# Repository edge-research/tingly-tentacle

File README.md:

# tingly-tentacle

# pololu stepper motor

- 1208 Stepper Motor: Bipolar, 200 Steps/Rev, 35×28mm, 10V, 0.5 A/Phase = 12.95
- https://www.pololu.com/product/1208

# pololu motor driver

- 2970 AMIS-30543 Stepper Motor Driver Carrier = 19.95
- https://www.pololu.com/product/2970
- http://www.onsemi.com/pub/Collateral/AMIS-30543-D.PDF
- https://github.com/pololu/amis-30543-arduino/

# blue robotics TSYS01

- https://github.com/bluerobotics/BlueRobotics_TSYS01_Library

# blue robotics MS5837

- http://docs.bluerobotics.com/bar30/
- https://github.com/bluerobotics/BlueRobotics_MS5837_Library

peristaltic pump system:
http://www.maschinenreich.com/wp-content/uploads/2017/03/XP88-Manual-A4-170320.pdf

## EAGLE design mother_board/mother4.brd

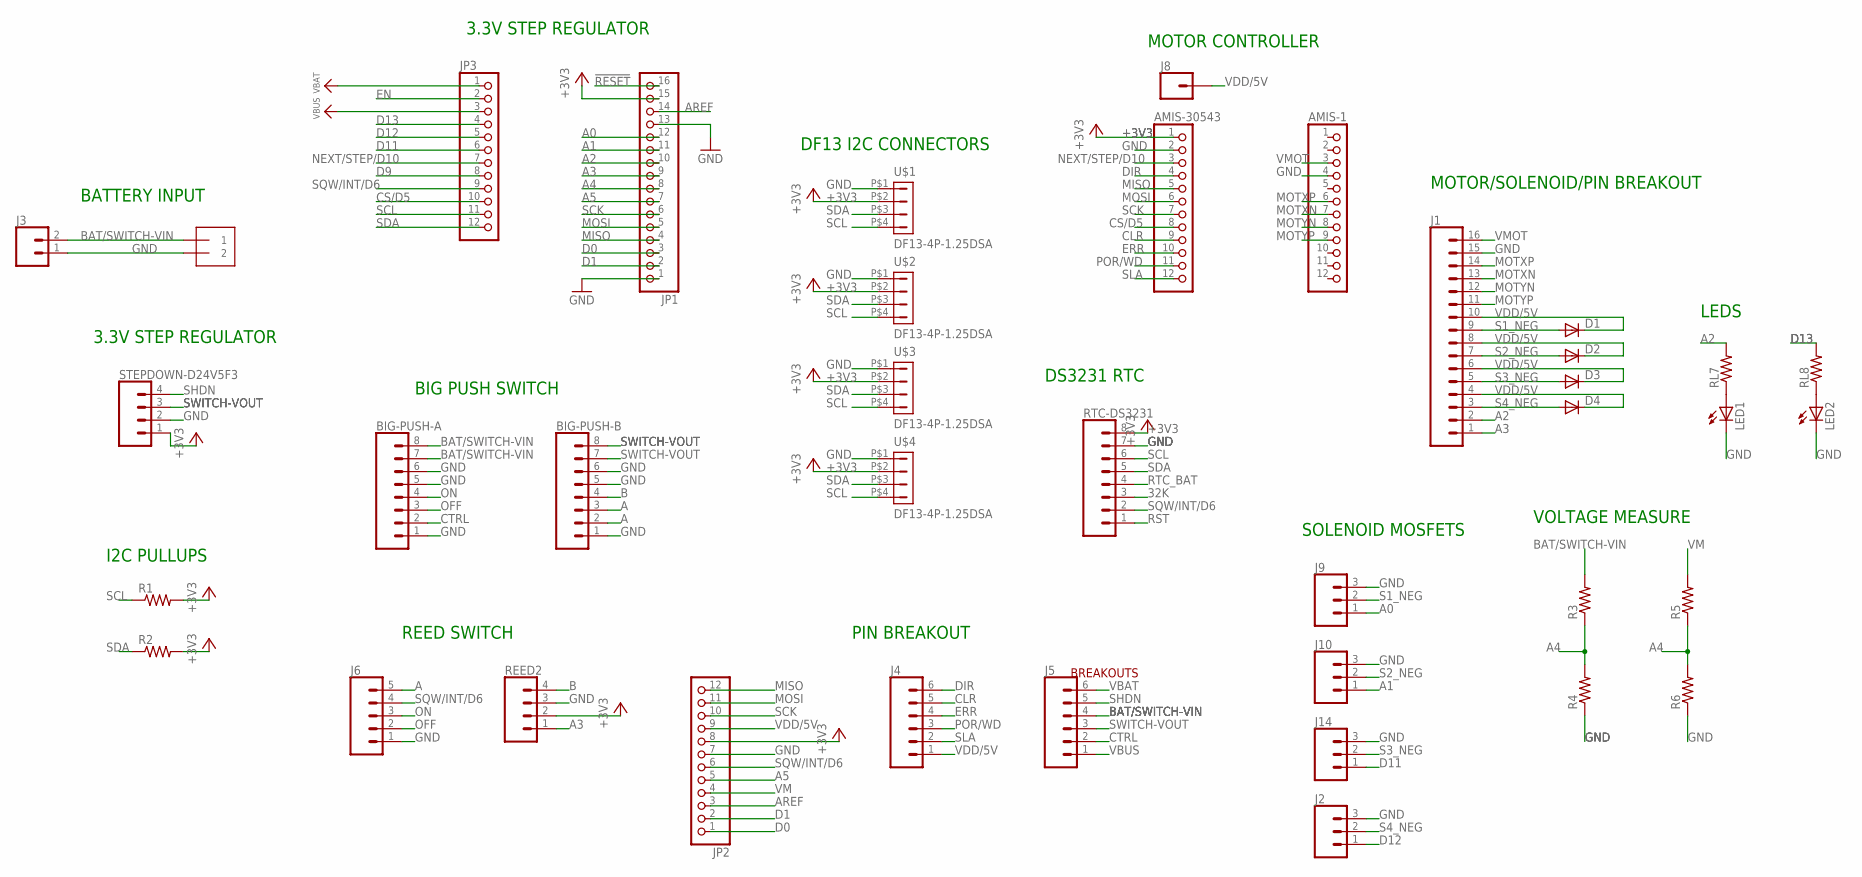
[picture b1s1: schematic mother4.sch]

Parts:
AMIS-1, AMIS-30543: PINHD-1X12-CB; 1X12-CB
BAT: 1X2-3.5MM
BIG-PUSH-A: CONN_08"; 1X08
BIG-PUSH-B: CONN_08"; 1X08
D1, D2, D3, D4: 1N4148DO35-7; DO35-7
J1: CONN_16; 1X16
J2, J9, J10, J14: CONN_03; 1X03
J3: CONN_02; 1X02
J4, J5: CONN_06SILK_FEMALE_PTH; 1X06
J6: CONN_05; 1X05
J8: CONN_01; 1X01
JP1: HEADER-1X16ROUND; 1X16_ROUND
JP2, JP3: HEADER-1X12; 1X12_ROUND
LED1, LED2: LED5MM
R1, R2, R3, R4, R5, R6: R-US_0207/10; 0207/10
REED2: CONN_04; 1X04
RL7, RL8: R-US_0207/10; 0207/10
RTC-DS3231: CONN_08"; 1X08
STEPDOWN-D24V5F3: CONN_04; 1X04
U$1, U$2, U$3, U$4: DF13-4P-1.25DSA

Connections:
32K: RTC-DS3231.3
!RESET: JP1.16
+3V3: AMIS-30543.1, JP1.15, JP2.8, R1.2, R2.2, REED2.2, RTC-DS3231.8, STEPDOWN-D24V5F3.1, U$1.P$2 (2), U$2.P$2 (2), U$3.P$2 (2), U$4.P$2 (2)
A: BIG-PUSH-B.2, BIG-PUSH-B.3, J6.5
A0: J9.1, JP1.12
A1: J10.1, JP1.11
A2: J1.2, JP1.10, RL7.2
A3: J1.1, JP1.9, REED2.1
A4: JP1.8, R3.1, R4.2, R5.1, R6.2
A5: JP1.7, JP2.5
AREF: JP1.14, JP2.3
B: BIG-PUSH-B.4, REED2.4
BAT/SWITCH-VIN: BAT.1, BIG-PUSH-A.7, BIG-PUSH-A.8, J3.2, J5.4, R3.2
CLR: AMIS-30543.9, J4.5
CS/D5: AMIS-30543.8, JP3.10
CTRL: BIG-PUSH-A.2, J5.2
D0: JP1.3, JP2.1
D1: JP1.2, JP2.2
D9: JP3.8
D11: J14.1, JP3.6
D12: J2.1, JP3.5
D13: JP3.4, RL8.2
DIR: AMIS-30543.4, J4.6
EN: JP3.2
ERR: AMIS-30543.10, J4.4
GND: AMIS-1.4, AMIS-30543.2, BAT.2, BIG-PUSH-A.1, BIG-PUSH-A.5, BIG-PUSH-A.6, BIG-PUSH-B.1, BIG-PUSH-B.5, BIG-PUSH-B.6, J1.15, J2.3, J3.1, J6.1, J9.3, J10.3, J14.3, JP1.1, JP1.13, JP2.7, LED1.K (C), LED2.K (C), R4.1, R6.1, REED2.3, RTC-DS3231.7, STEPDOWN-D24V5F3.2, U$1.P$1 (1), U$2.P$1 (1), U$3.P$1 (1), U$4.P$1 (1)
MISO: AMIS-30543.5, JP1.4, JP2.12
MOSI: AMIS-30543.6, JP1.5, JP2.11
MOTXN: AMIS-1.7, J1.13
MOTXP: AMIS-1.6, J1.14
MOTYN: AMIS-1.8, J1.12
MOTYP: AMIS-1.9, J1.11
unnamed: LED1.A, RL7.1
unnamed: LED2.A, RL8.1
NEXT/STEP/D10: AMIS-30543.3, JP3.7
OFF: BIG-PUSH-A.3, J6.2
ON: BIG-PUSH-A.4, J6.3
POR/WD: AMIS-30543.11, J4.3
RST: RTC-DS3231.1
RTC_BAT: RTC-DS3231.4
S1_NEG: D1.A, J1.9, J9.2
S2_NEG: D2.A, J1.7, J10.2
S3_NEG: D3.A, J1.5, J14.2
S4_NEG: D4.A, J1.3, J2.2
SCK: AMIS-30543.7, JP1.6, JP2.10
SCL: JP3.11, R1.1, RTC-DS3231.6, U$1.P$4 (4), U$2.P$4 (4), U$3.P$4 (4), U$4.P$4 (4)
SDA: JP3.12, R2.1, RTC-DS3231.5, U$1.P$3 (3), U$2.P$3 (3), U$3.P$3 (3), U$4.P$3 (3)
SHDN: J5.5, STEPDOWN-D24V5F3.4
SLA: AMIS-30543.12, J4.2
SQW/INT/D6: J6.4, JP2.6, JP3.9, RTC-DS3231.2
SWITCH-VOUT: BIG-PUSH-B.7, BIG-PUSH-B.8, J5.3, STEPDOWN-D24V5F3.3
VBAT: J5.6, JP3.1
VBUS: J5.1, JP3.3
VDD/5V: D1.C, D2.C, D3.C, D4.C, J1.4, J1.6, J1.8, J1.10, J4.1, J8.1, JP2.9
VM: JP2.4, R5.2
VMOT: AMIS-1.3, J1.16

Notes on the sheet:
BREAKOUTS
BATTERY INPUT
3.3V STEP REGULATOR
BIG PUSH SWITCH
REED SWITCH
PIN BREAKOUT
DS3231 RTC
SOLENOID MOSFETS
MOTOR/SOLENOID/PIN BREAKOUT
MOTOR CONTROLLER
I2C PULLUPS
DF13 I2C CONNECTORS
VOLTAGE MEASURE
LEDS

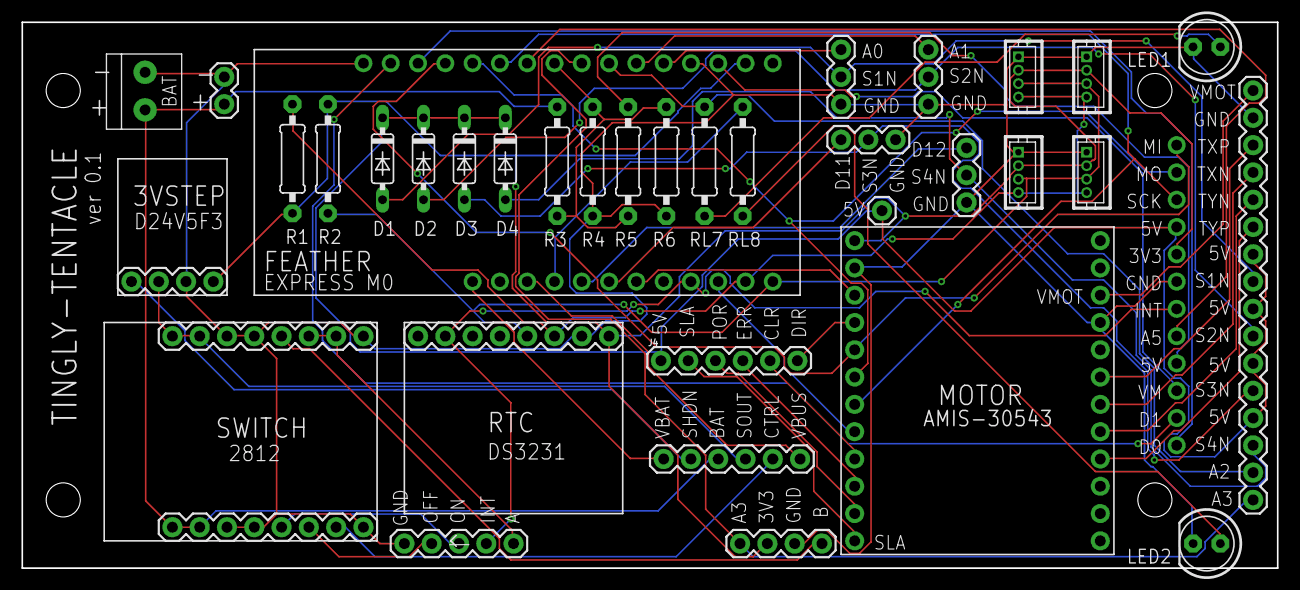
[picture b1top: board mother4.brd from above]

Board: 2 copper layers, 116.8 x 50.8 mm, 39 parts (0 on the bottom side), 50 nets.

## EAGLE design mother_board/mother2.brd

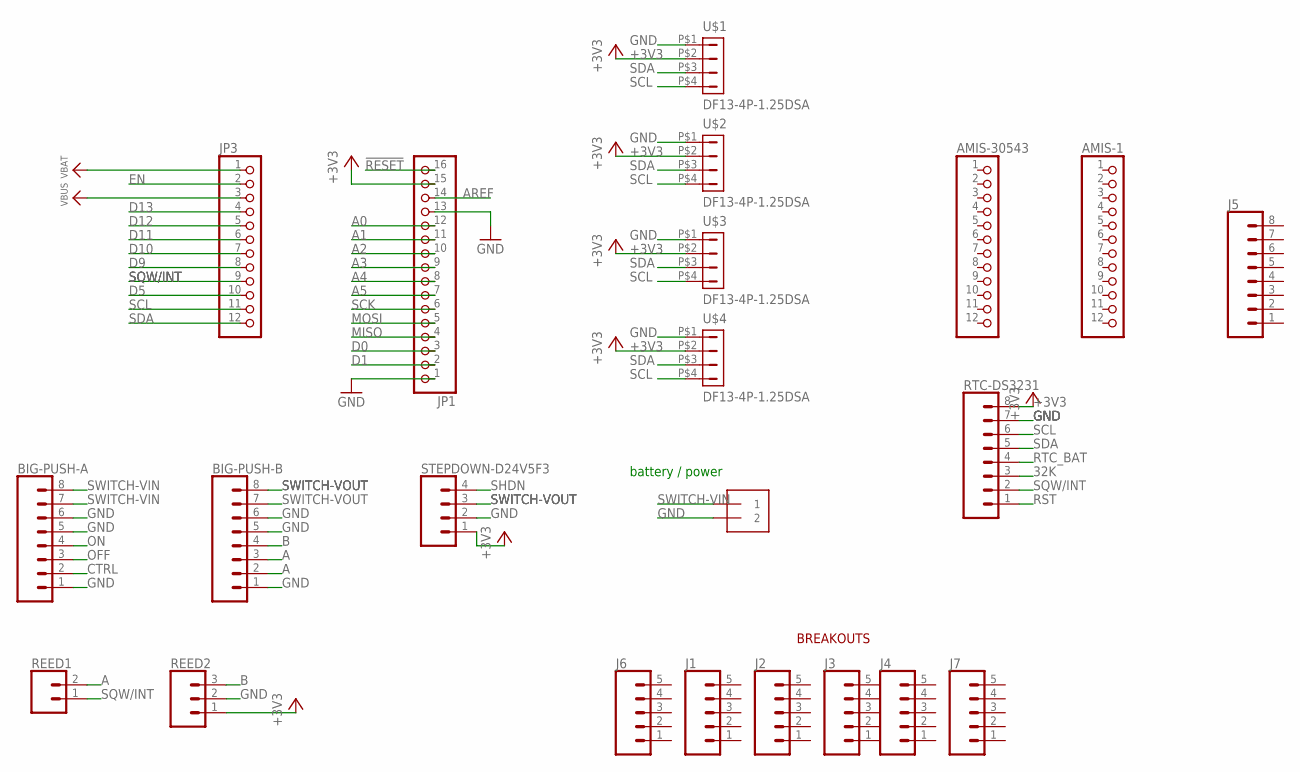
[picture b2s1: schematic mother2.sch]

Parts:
AMIS-1, AMIS-30543: PINHD-1X12-CB; 1X12-CB
BAT: 1X2-3.5MM
BIG-PUSH-A: CONN_08"; 1X08
BIG-PUSH-B: CONN_08"; 1X08
J1, J2, J3, J4, J6, J7: CONN_05; 1X05
J5: CONN_08"; 1X08
JP1: HEADER-1X16ROUND; 1X16_ROUND
JP3: HEADER-1X12; 1X12_ROUND
REED1: CONN_02; 1X02
REED2: CONN_03; 1X03
RTC-DS3231: CONN_08"; 1X08
STEPDOWN-D24V5F3: CONN_04; 1X04
U$1, U$2, U$3, U$4: DF13-4P-1.25DSA

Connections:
32K: RTC-DS3231.3
!RESET: JP1.16
+3V3: JP1.15, REED2.1, RTC-DS3231.8, STEPDOWN-D24V5F3.1, U$1.P$2 (2), U$2.P$2 (2), U$3.P$2 (2), U$4.P$2 (2)
A: BIG-PUSH-B.2, BIG-PUSH-B.3, REED1.2
A0: JP1.12
A1: JP1.11
A2: JP1.10
A3: JP1.9
A4: JP1.8
A5: JP1.7
AREF: JP1.14
B: BIG-PUSH-B.4, REED2.3
CTRL: BIG-PUSH-A.2
D0: JP1.3
D1: JP1.2
D5: JP3.10
D9: JP3.8
D10: JP3.7
D11: JP3.6
D12: JP3.5
D13: JP3.4
EN: JP3.2
GND: BAT.2, BIG-PUSH-A.1, BIG-PUSH-A.5, BIG-PUSH-A.6, BIG-PUSH-B.1, BIG-PUSH-B.5, BIG-PUSH-B.6, JP1.1, JP1.13, REED2.2, RTC-DS3231.7, STEPDOWN-D24V5F3.2, U$1.P$1 (1), U$2.P$1 (1), U$3.P$1 (1), U$4.P$1 (1)
MISO: JP1.4
MOSI: JP1.5
OFF: BIG-PUSH-A.3
ON: BIG-PUSH-A.4
RST: RTC-DS3231.1
RTC_BAT: RTC-DS3231.4
SCK: JP1.6
SCL: JP3.11, RTC-DS3231.6, U$1.P$4 (4), U$2.P$4 (4), U$3.P$4 (4), U$4.P$4 (4)
SDA: JP3.12, RTC-DS3231.5, U$1.P$3 (3), U$2.P$3 (3), U$3.P$3 (3), U$4.P$3 (3)
SHDN: STEPDOWN-D24V5F3.4
SQW/INT: JP3.9, REED1.1, RTC-DS3231.2
SWITCH-VIN: BAT.1, BIG-PUSH-A.7, BIG-PUSH-A.8
SWITCH-VOUT: BIG-PUSH-B.7, BIG-PUSH-B.8, STEPDOWN-D24V5F3.3
VBAT: JP3.1
VBUS: JP3.3

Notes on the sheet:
BREAKOUTS
battery / power

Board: 2 copper layers, 22 parts (0 on the bottom side), 9 nets, no tracks yet.

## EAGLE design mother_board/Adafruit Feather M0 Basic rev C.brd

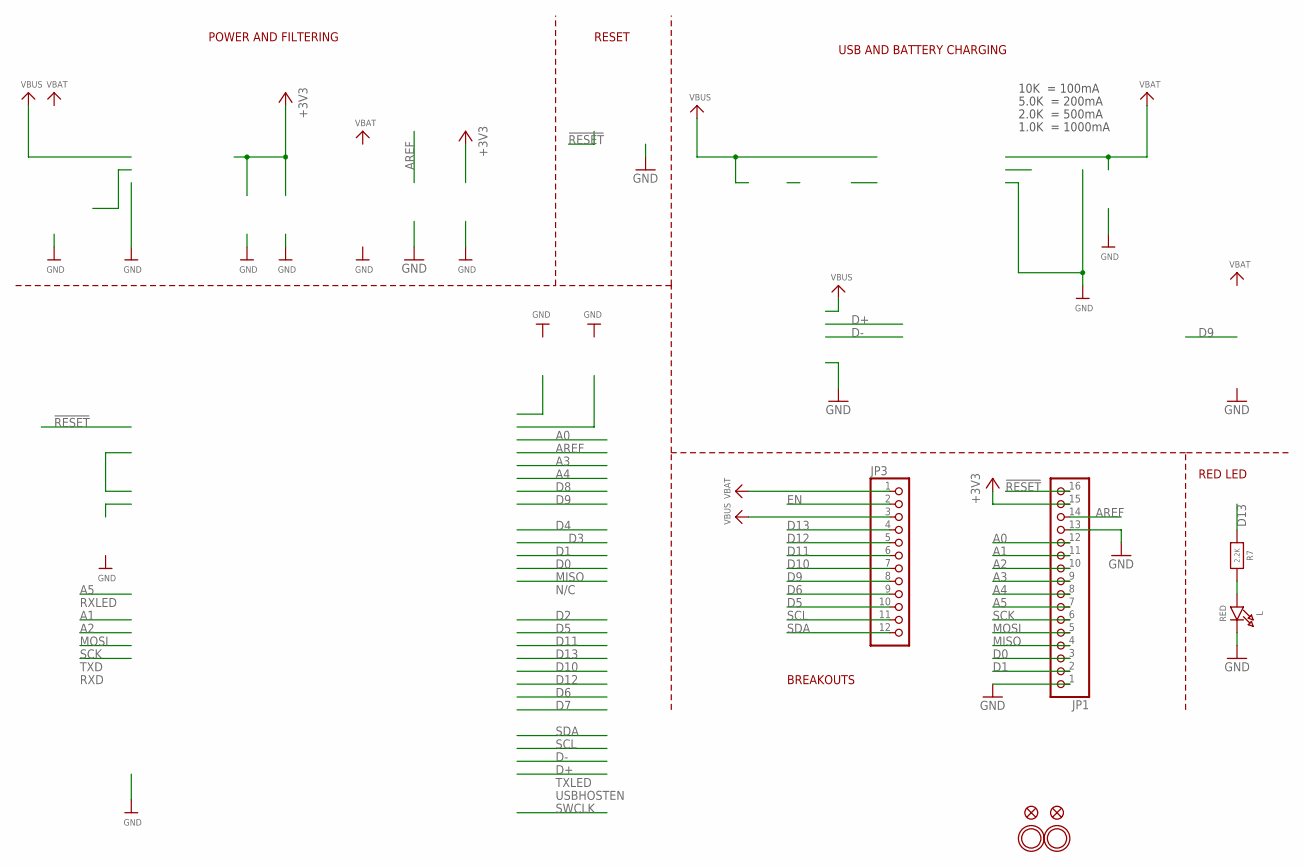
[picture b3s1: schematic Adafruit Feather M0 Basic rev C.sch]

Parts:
JP1: HEADER-1X16ROUND; 1X16_ROUND
JP3: HEADER-1X12; 1X12_ROUND
L: RED; CHIPLED_0805_NOOUTLINE
R7: 2.2K; 0603-NO
U$31, U$32: MOUNTINGHOLE2.5; MOUNTINGHOLE_2.5_PLATED
U$34, U$35: FIDUCIAL""; FIDUCIAL_1MM

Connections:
!RESET: JP1.16
+3V3: JP1.15
A0: JP1.12
A1: JP1.11
A2: JP1.10
A3: JP1.9
A4: JP1.8
A5: JP1.7
AREF: JP1.14
D0: JP1.3
D1: JP1.2
D5: JP3.10
D6: JP3.9
D9: JP3.8
D10: JP3.7
D11: JP3.6
D12: JP3.5
D13: JP3.4, R7.1
EN: JP3.2
GND: JP1.1, JP1.13, L.C
MISO: JP1.4
MOSI: JP1.5
unnamed: L.A, R7.2
SCK: JP1.6
SCL: JP3.11
SDA: JP3.12
VBAT: JP3.1
VBUS: JP3.3

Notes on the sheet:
POWER AND FILTERING
RESET
10K = 100mA
5.0K = 200mA
2.0K = 500mA
1.0K = 1000mA
N/C
TXLED
USBHOSTEN
RXLED
TXD
RXD
USB AND BATTERY CHARGING
BREAKOUTS
RED LED

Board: 2 copper layers, 12 parts (3 on the bottom side), 3 nets, no tracks yet.

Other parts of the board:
U$7, U$12: ADAFRUIT_3.5MM
U$9: FEATHERLOGO
U$13: PCBFEAT-REV-040

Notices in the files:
parts and their libraries:
microbuilder: This work is placed in the public domain, and may be freely used for commercial and non-commercial work with the following conditions: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
SparkFun-Connectors: Licensing: Creative Commons ShareAlike 4.0 International - https://creativecommons.org/licenses/by-sa/4.0
